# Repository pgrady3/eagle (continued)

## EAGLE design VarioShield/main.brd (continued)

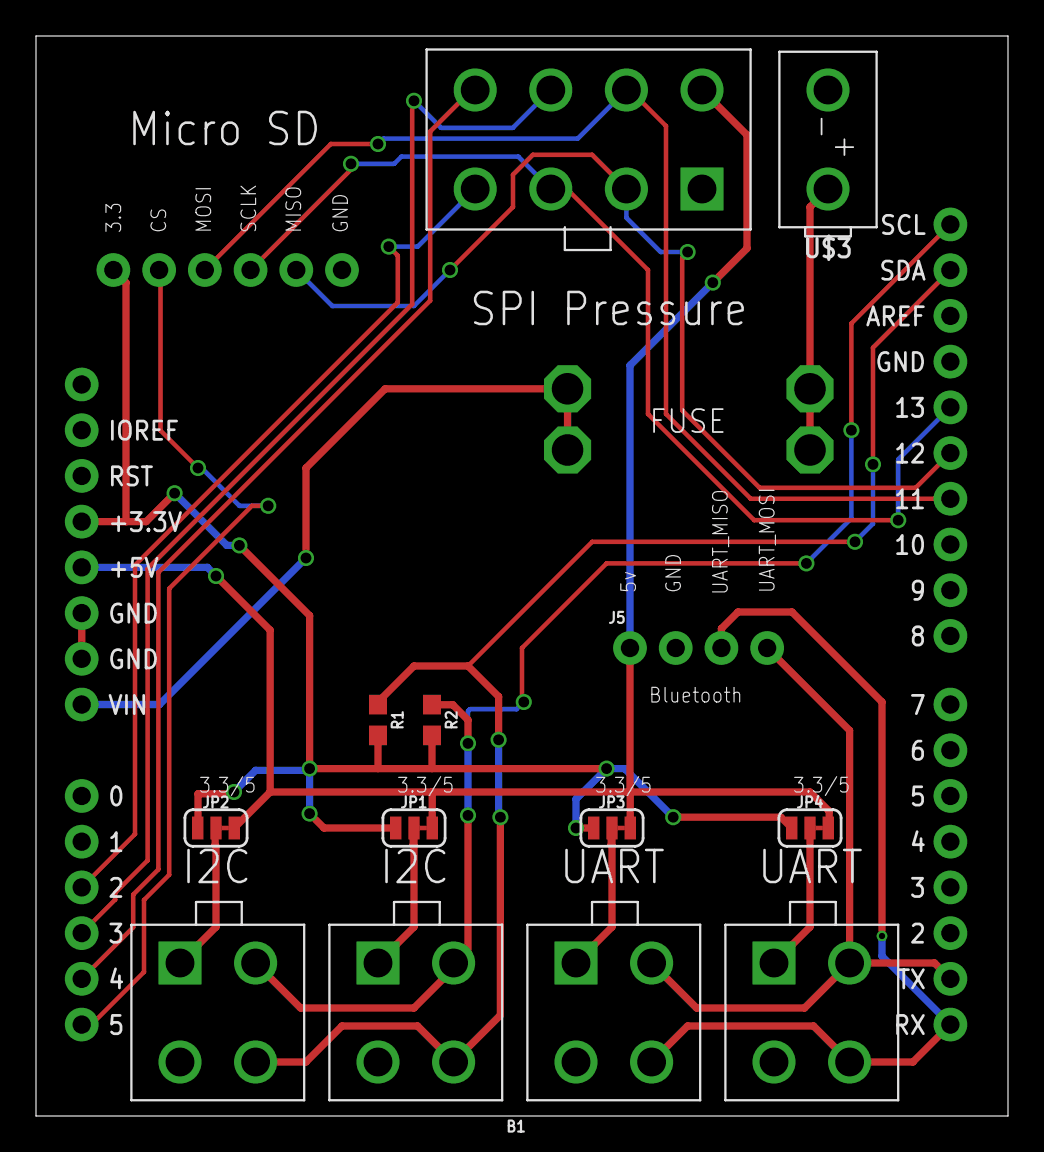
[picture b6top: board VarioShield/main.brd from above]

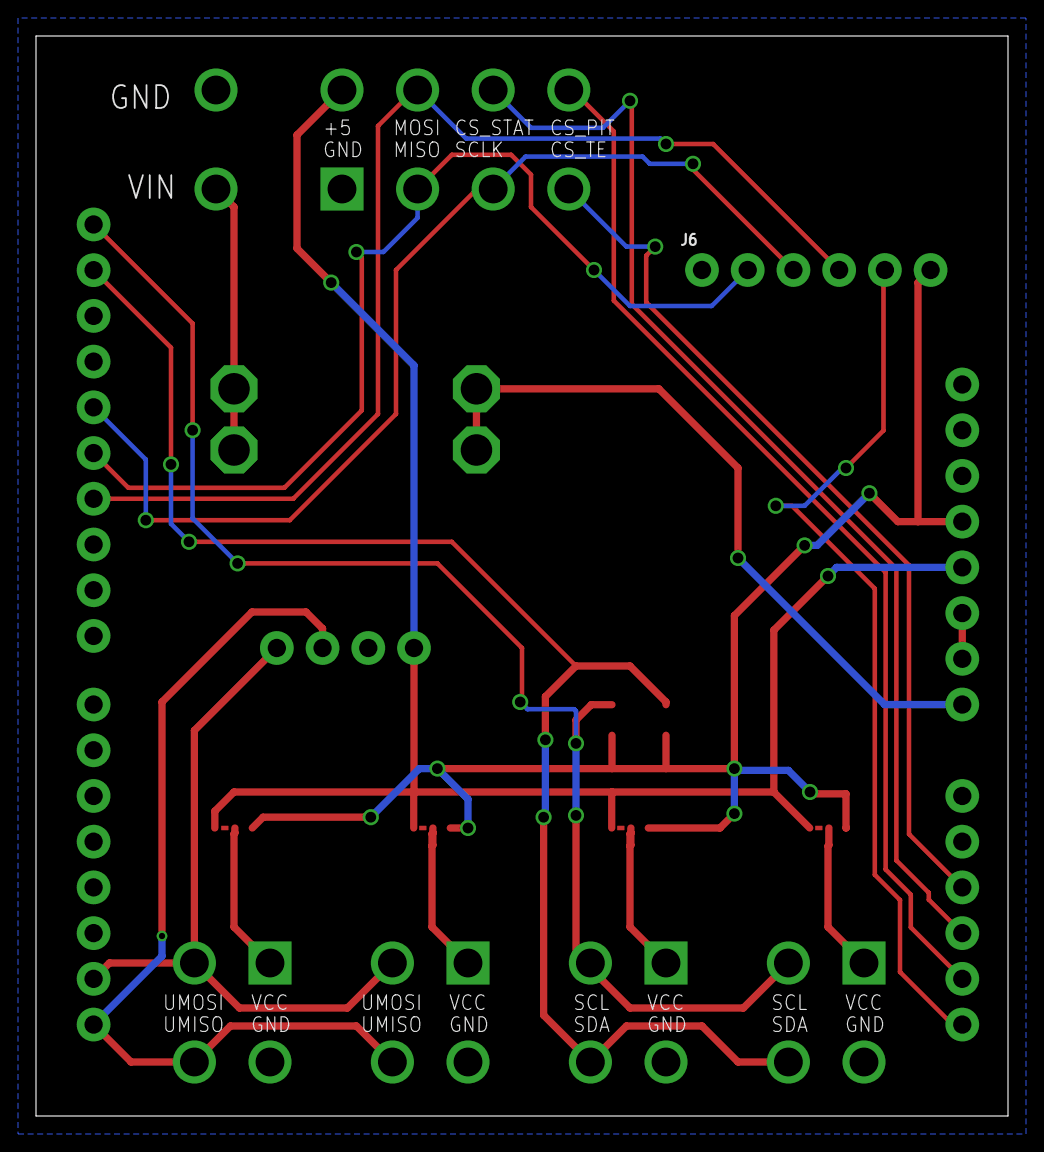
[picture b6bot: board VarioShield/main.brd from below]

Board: 2 copper layers, 54.0 x 60.0 mm, 16 parts (2 on the bottom side), 20 nets.

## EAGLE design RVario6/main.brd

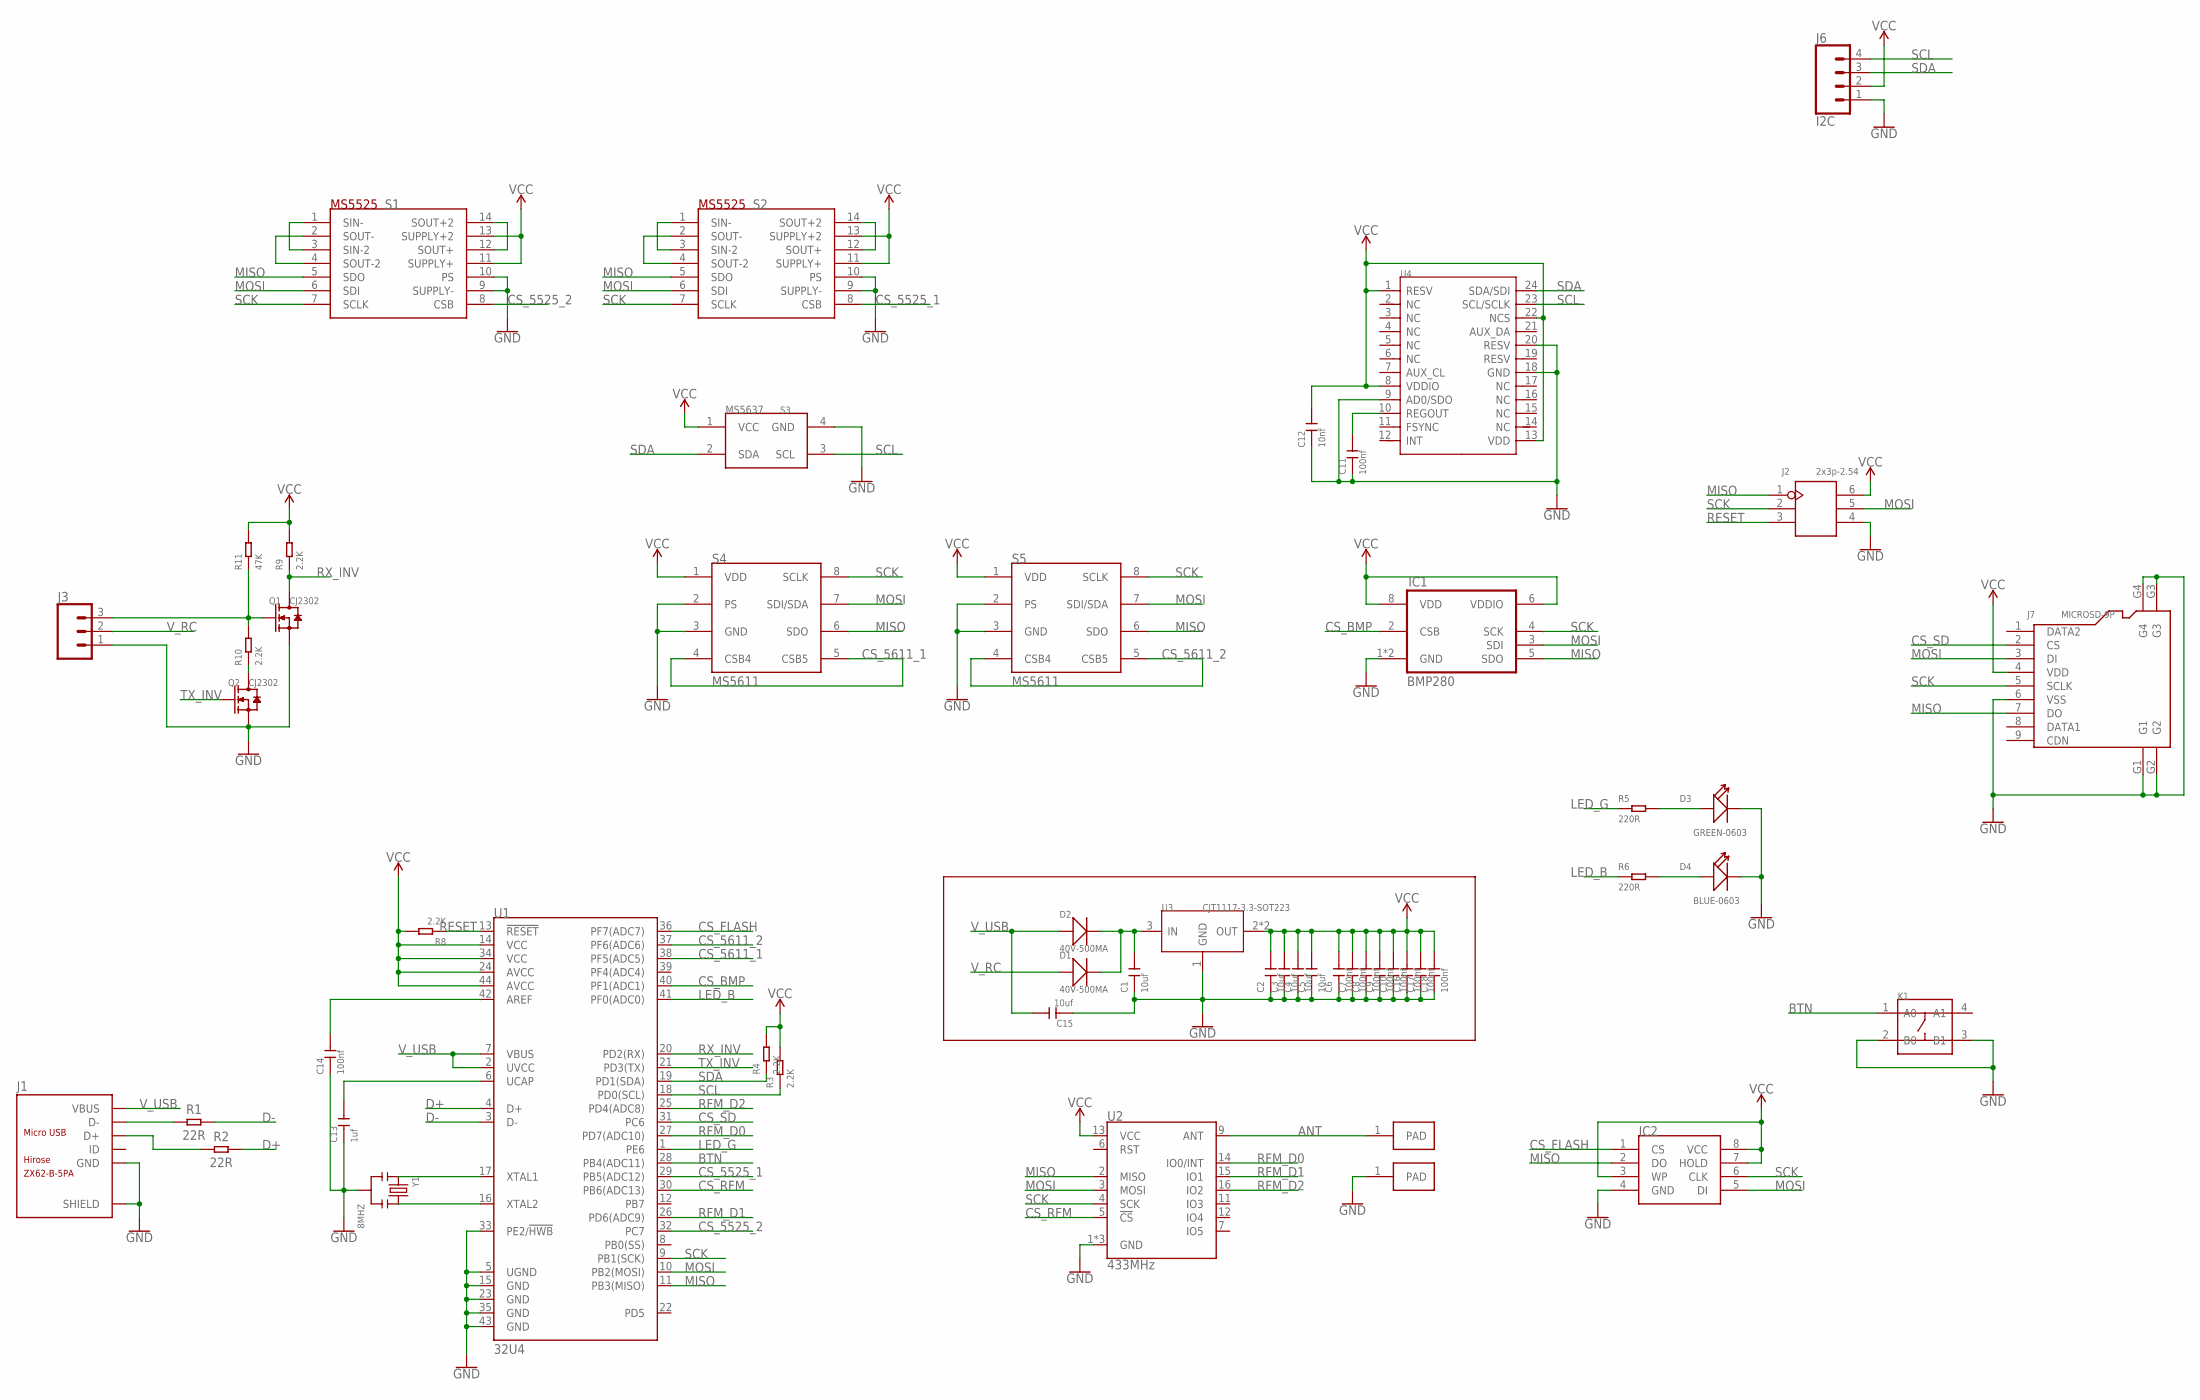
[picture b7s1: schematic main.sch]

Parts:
C1, C2, C3, C4, C5, C15: 10uf; C0805
C6, C7, C8, C9, C10, C11, C14, C16, C17, C18: 100nf; C0603
C12: 10nf; C0603
C13: 1uf; C0603
D1, D2: 40V-500MA; SOD-123
D3: GREEN-0603; LED-0603
D4: BLUE-0603; LED-0603
IC1: BMP280
IC2: W25Q32BVWSON8_6X5; SON127P600X500X75-8
J1: ZX62-B-5PA; MICRO-USB5+6P-SMD-0.65-AB
J2: 2x3p-2.54; H2X3-2.54
J3: CONN_03; 1X03
J6: I2C; 1X04
J7: MICROSD-9P; MICRO-SD9+4P-SMD-16.1X14.5X1.85MM
K1: SMD-SWITCH-TACTILE-SPST-NO(4P-D6.0MM); SW4-SMD-6.0X6.0X5.0MM
Q1, Q2: CJ2302; SOT-23
R1, R2: 22R; R0603
R3, R4, R8, R9, R10: 2.2K; R0603
R5, R6: 220R; R0603
R11: 47K; R0603
S1, S2: MS5525; SOIC14-WIDE
S3: MS5637
S4, S5: MS5611
U1: 32U4; QFN-44-NOPAD_1:1
U2: 433MHz; RFM69HCW-XXXS2
U3: CJT1117-3.3-SOT223; SOT-223
U4: MOTION/POSITION-MPU-9250(QFN24G); QFN24G-0.4-3X3MM
U$1, U$2: PADPAD_2.5X1.5; PAD_2.5X1.5
Y1: 8MHZ; X3-SMD-3.6X1.3X0.8MM

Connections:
ANT: U2.9 (ANT), U$2.1
BTN: K1.1 (A0), U1.28 (PB4(ADC11))
CS_5525_1: S2.8 (CSB), U1.29 (PB5(ADC12))
CS_5525_2: S1.8 (CSB), U1.32 (PC7)
CS_5611_1: S4.4 (CSB4), S4.5 (CSB5), U1.38 (PF5(ADC5))
CS_5611_2: S5.4 (CSB4), S5.5 (CSB5), U1.37 (PF6(ADC6))
CS_BMP: IC1.2 (CSB), U1.40 (PF1(ADC1))
CS_FLASH: IC2.1 (CS), U1.36 (PF7(ADC7))
CS_RFM: U1.30 (PB6(ADC13)), U2.5 (!CS)
CS_SD: J7.2 (CS), U1.31 (PC6)
D+: R2.2, U1.4 (D+)
D-: R1.2, U1.3 (D-)
GND: C1.1, C2.1, C3.1, C4.1, C5.1, C6.1, C7.1, C8.1, C9.1, C10.1, C11.1, C12.1, C13.1, C14.1, C15.1, C16.1, C17.1, C18.1, D3.-, D4.-, IC1.1 (GND), IC1.7 (GND), IC2.4 (GND), J1.5 (GND), J1.P1 (SHIELD), J1.P2 (SHIELD), J1.P3 (SHIELD), J1.P4 (SHIELD), J1.P5 (SHIELD), J1.P6 (SHIELD), J2.4, J3.1, J6.1, J7.6 (VSS), J7.G1, J7.G2, J7.G3, J7.G4, K1.2 (B0), K1.3 (B1), Q1.2 (S), Q2.2 (S), S1.9 (SUPPLY-), S1.10 (PS), S2.9 (SUPPLY-), S2.10 (PS), S3.4 (GND), S4.2 (PS), S4.3 (GND), S5.2 (PS), S5.3 (GND), U1.5 (UGND), U1.15 (GND), U1.23 (GND), U1.33 (PE2/!HWB), U1.35 (GND), U1.43 (GND), U2.1 (GND), U2.8 (GND), U2.10 (GND), U3.1 (GND), U4.9 (AD0/SDO), U4.18 (GND), U4.20 (RESV), U$1.1, Y1.2
LED_B: R6.1, U1.41 (PF0(ADC0))
LED_G: R5.1, U1.1 (PE6)
MISO: IC1.5 (SDO), IC2.2 (DO), J2.1, J7.7 (DO), S1.5 (SDO), S2.5 (SDO), S4.6 (SDO), S5.6 (SDO), U1.11 (PB3(MISO)), U2.2 (MISO)
MOSI: IC1.3 (SDI), IC2.5 (DI), J2.5, J7.3 (DI), S1.6 (SDI), S2.6 (SDI), S4.7 (SDI/SDA), S5.7 (SDI/SDA), U1.10 (PB2(MOSI)), U2.3 (MOSI)
unnamed: U1.17 (XTAL1), Y1.1
unnamed: U1.16 (XTAL2), Y1.3
unnamed: J1.2 (D-), R1.1
unnamed: J1.3 (D+), R2.1
unnamed: C1.2, D1.-, D2.-, U3.3 (IN)
unnamed: Q2.3 (D), R10.1
unnamed: S2.1 (SIN-), S2.3 (SIN-2)
unnamed: S2.2 (SOUT-), S2.4 (SOUT-2)
unnamed: S2.12 (SOUT+), S2.14 (SOUT+2)
unnamed: C11.2, U4.10 (REGOUT)
unnamed: S1.1 (SIN-), S1.3 (SIN-2)
unnamed: S1.2 (SOUT-), S1.4 (SOUT-2)
unnamed: S1.12 (SOUT+), S1.14 (SOUT+2)
unnamed: D3.+, R5.2
unnamed: D4.+, R6.2
unnamed: C13.2, U1.6 (UCAP)
unnamed: C14.2, U1.42 (AREF)
RC_IN: J3.3, Q1.1 (G), R10.2, R11.1
RESET: J2.3, R8.1, U1.13 (!RESET)
RFM_D0: U1.27 (PD7(ADC10)), U2.14 (IO0/INT)
RFM_D1: U1.26 (PD6(ADC9)), U2.15 (IO1)
RFM_D2: U1.25 (PD4(ADC8)), U2.16 (IO2)
RX_INV: Q1.3 (D), R9.1, U1.20 (PD2(RX))
SCK: IC1.4 (SCK), IC2.6 (CLK), J2.2, J7.5 (SCLK), S1.7 (SCLK), S2.7 (SCLK), S4.8 (SCLK), S5.8 (SCLK), U1.9 (PB1(SCK)), U2.4 (SCK)
SCL: J6.4, R3.1, S3.3 (SCL), U1.18 (PD0(SCL)), U4.23 (SCL/SCLK)
SDA: J6.3, R4.1, S3.2 (SDA), U1.19 (PD1(SDA)), U4.24 (SDA/SDI)
TX_INV: Q2.1 (G), U1.21 (PD3(TX))
VCC: C2.2, C3.2, C4.2, C5.2, C6.2, C7.2, C8.2, C9.2, C10.2, C12.2, C16.2, C17.2, C18.2, IC1.6 (VDDIO), IC1.8 (VDD), IC2.3 (WP), IC2.7 (HOLD), IC2.8 (VCC), J2.6, J6.2, J7.4 (VDD), R3.2, R4.2, R8.2, R9.2, R11.2, S1.11 (SUPPLY+), S1.13 (SUPPLY+2), S2.11 (SUPPLY+), S2.13 (SUPPLY+2), S3.1 (VCC), S4.1 (VDD), S5.1 (VDD), U1.14 (VCC), U1.24 (AVCC), U1.34 (VCC), U1.44 (AVCC), U2.13 (VCC), U3.2 (OUT), U3.TER (OUT), U4.1 (RESV), U4.8 (VDDIO), U4.13 (VDD), U4.22 (NCS)
V_RC: D1.+, J3.2
V_USB: C15.2, D2.+, J1.1 (VBUS), U1.2 (UVCC), U1.7 (VBUS)

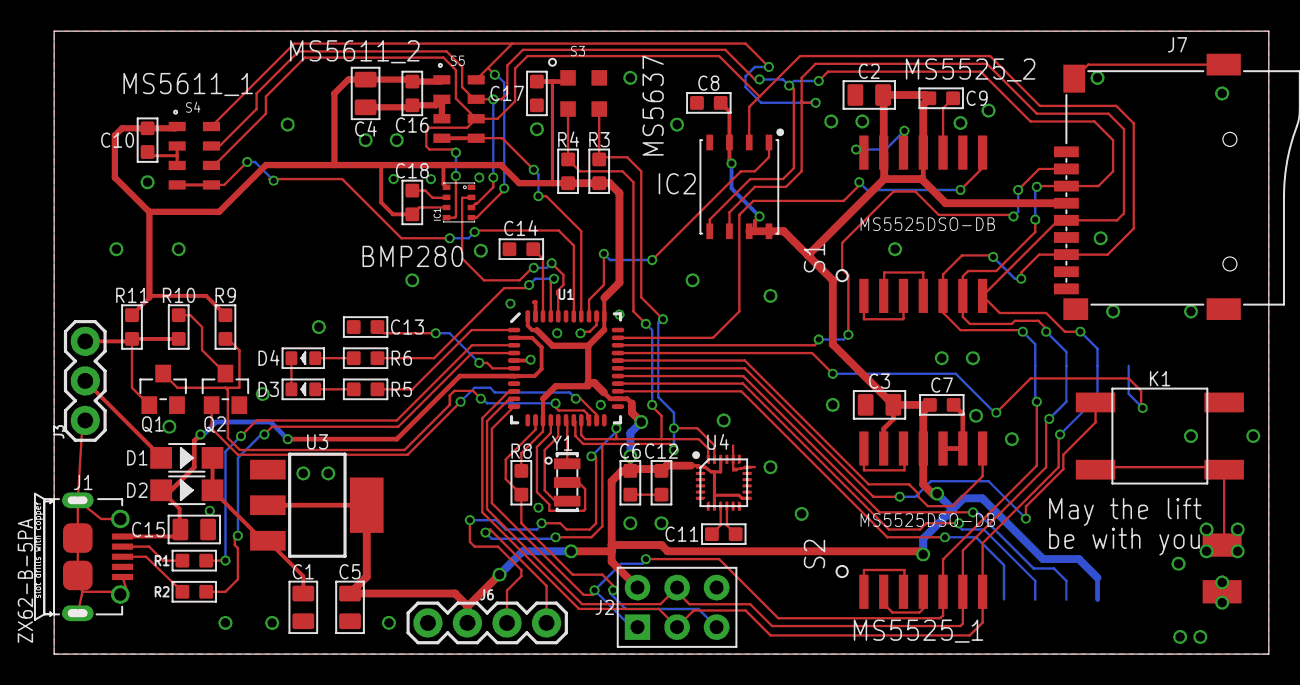
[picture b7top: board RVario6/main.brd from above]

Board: 2 copper layers, 78.6 x 40.0 mm, 54 parts (1 on the bottom side), 47 nets.

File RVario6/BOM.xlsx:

Designator | MPN/Seeed SKU | Qty | Link | Price
U1 | ATMEGA32U4-MUR | 1 | 310010016 | 4.0999999999999996 | AVR |  |  |  |  | 4.0999999999999996 |  | 9.2879999999999967
J1 | ZX62D-B-5P8 | 1 | 320010005 | 0.12 | Micro USB |  |  |  |  | 0.12
R1,R2 | RC0603JR-0722RL | 2 | 301010289 | 0.01 | 22 ohm 0603 |  |  |  |  | 0.02
Y1 | CSTCE8M00G55-RO | 1 | 306010053 | 0.188 | 8MHz crystal |  |  |  |  | 0.188
D1,D2 | B0540W | 2 | 304020012 | 0.03 | Schottkey |  |  |  |  | 0.06
U3 | CJT1117-3.3 | 1 | 310030097 | 0.08 | 3.3V VREG |  |  |  |  | 0.08
C1,C2,C3,C4,C5,C15 | CC0805KKX5R8BB106 | 6 | 302010178 | 0.02 | 10uF cap |  |  |  |  | 0.12
C6,C7,C8,C9,C10,C11,C14,C16,C17,C18 | CC0603KRX7R9BB104 | 10 | 302010138 | 0.01 | 0.1uF cap |  |  |  |  | 0.1
R3,R4,R8,R9,R10 | RC0603JR-072K2L | 5 | 301010124 | 0.01 | 2.2k res |  |  |  |  | 0.05
C12 | CC0603KRX7R9BB103 | 1 | 302010140 | 0.01 | 10nF cap |  |  |  |  | 0.01
IC1 | BMP280 | 1 | 314030010 | 1.07 | BMP280 |  |  |  |  | 1.07
D3 | 19-217-G7C-AN1P2-3T | 1 | 304090043 | 0.02 | LED GREEN |  |  |  |  | 0.02
D4 | 19-217-BHC-ZL1M2RY-3T | 1 | 304090045 | 0.02 | LED BLUE |  |  |  |  | 0.02
R5,R6 | RC0603JR-07220RL | 2 | 301010163 | 0.01 | 220 ohm |  |  |  |  | 0.02
J2 | P125-12A1BS116A1 | 1 | 320020077 | 0.01 | ISP header |  |  |  |  | 0.01
IC2 | W25Q32BVZPIP | 1 | 310090078 | 0.26 | 4MB flash |  |  |  |  | 0.26
C13 | CC0603KRX7R8BB105 | 1 | 302010139 | 0.01 | 1uF cap |  |  |  |  | 0.01
U4 | MPU-9250 | 1 | 314990005 | 2.8 | MPU9250 |  |  |  |  | 2.8
K1 | DTSM-62K-S-V-T/R | 1 | 311020004 | 0.05 | SMD btn |  |  |  |  | 0.05
J7 | TF-01 | 1 | 320090008 | 0.11 | SD card holder |  |  |  |  | 0.11
Q1,Q2 | CJ2302 | 2 | 305030015 | 0.03 | NFET |  |  |  |  | 0.06
R11 | RC0603JR-0747KL | 1 | 301010084 | 0.01 | 47k resistor |  |  |  |  | 0.01
 |  |  |  |  |  |  |  |  |  | 0
 |  |  |  |  |  |  |  |  |  | 0
 |  |  |  |  |  |  |  |  |  | 0
 |  |  |  |  |  |  |  |  |  | 0
 |  |  |  |  |  |  |  |  |  | 0
 |  |  |  |  |  |  |  |  |  | 0

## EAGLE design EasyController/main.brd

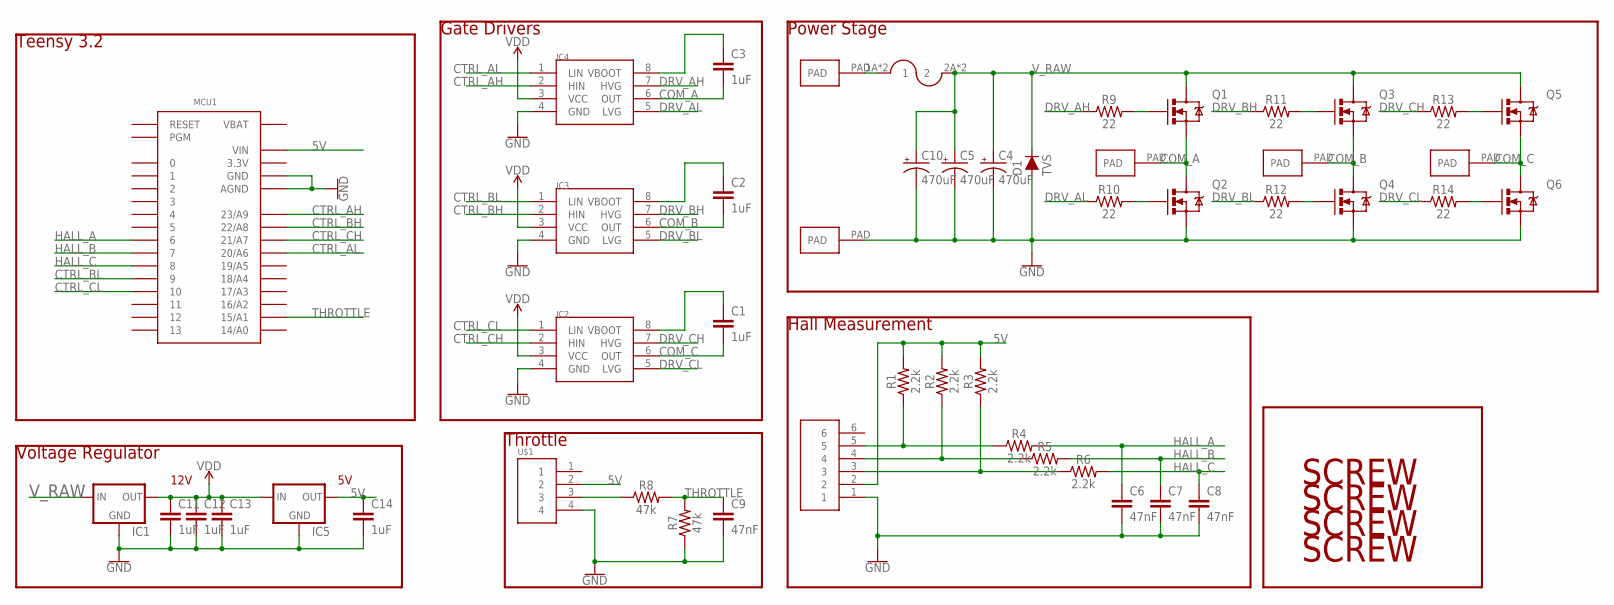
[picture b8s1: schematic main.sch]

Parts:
C1, C2, C3, C11, C12, C13, C14: 1uF; CAP-PTH-SMALL-KIT
C4, C5, C10: 470uF; CPOL-RADIAL-5MM-10MM
C6, C7, C8, C9: 47nF; CAP-PTH-SMALL-KIT
D1: TVS; DIODE-1N4001
IC1: V_REG_78XX; V78W_BACKWARDS
IC2, IC3, IC4: L6387EDIP8; DIP762W53P254L1092H508Q8B
IC5: V_REG_78XXTO-92_UNTESTED; TO-92
J3: FUSE; AUTO_FUSE
MCU1: TEENSY_3.0_BASIC
Q1, Q2, Q3, Q4, Q5, Q6: MOSFET-NCHANNELTO-220-FLAT; TO-220-FLAT
R1, R2, R3, R4, R5, R6: 2.2k; AXIAL-0.3
R7, R8: 47k; AXIAL-0.3
R9, R10, R11, R12, R13, R14: 22; AXIAL-0.3
U$1: HEADER4VALULOK; 4PINVALULOK
U$2: HEADER6; 6PINVALULOK
U$4, U$5, U$6, U$7, U$8: PAD
U$10, U$11, U$12, U$13: SCREW; M3HOLE

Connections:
3.3V: MCU1.3.3V, MCU1.3.3V1 (3.3V)
5V: C14.1, IC5.1 (OUT), MCU1.VIN, R1.P$2 (2), R2.P$2 (2), R3.P$2 (2), U$1.2, U$2.2
COM_A: C3.2, IC4.6 (OUT), Q1.3 (S), Q2.2 (D), Q2.PAD (D), U$6.PAD
COM_B: C2.2, IC3.6 (OUT), Q3.3 (S), Q4.2 (D), Q4.PAD (D), U$7.PAD
COM_C: C1.2, IC2.6 (OUT), Q5.3 (S), Q6.2 (D), Q6.PAD (D), U$8.PAD
CTRL_AH: IC4.2 (HIN), MCU1.23/A9
CTRL_AL: IC4.1 (LIN), MCU1.20/A6
CTRL_BH: IC3.2 (HIN), MCU1.22/A8
CTRL_BL: IC3.1 (LIN), MCU1.9
CTRL_CH: IC2.2 (HIN), MCU1.21/A7
CTRL_CL: IC2.1 (LIN), MCU1.10
DRV_AH: IC4.7 (HVG), R9.P$1 (1)
DRV_AL: IC4.5 (LVG), R10.P$1 (1)
DRV_BH: IC3.7 (HVG), R11.P$1 (1)
DRV_BL: IC3.5 (LVG), R12.P$1 (1)
DRV_CH: IC2.7 (HVG), R13.P$1 (1)
DRV_CL: IC2.5 (LVG), R14.P$1 (1)
GND: C4.-, C5.-, C6.2, C7.2, C8.2, C9.2, C10.-, C11.2, C12.2, C13.2, C14.2, D1.A, IC1.GND, IC2.4 (GND), IC3.4 (GND), IC4.4 (GND), IC5.2 (GND), MCU1.AGND, MCU1.GND, MCU1.GND1 (GND), Q2.3 (S), Q4.3 (S), Q6.3 (S), R7.P$1 (1), U$1.4, U$2.1, U$5.PAD
HALL_A: C6.1, MCU1.6, R4.P$2 (2)
HALL_B: C7.1, MCU1.7, R5.P$2 (2)
HALL_C: C8.1, MCU1.8, R6.P$2 (2)
unnamed: C1.1, IC2.8 (VBOOT)
unnamed: R3.P$1 (1), R6.P$1 (1), U$2.3
unnamed: C2.1, IC3.8 (VBOOT)
unnamed: R2.P$1 (1), R5.P$1 (1), U$2.4
unnamed: C3.1, IC4.8 (VBOOT)
unnamed: R1.P$1 (1), R4.P$1 (1), U$2.5
unnamed: R8.P$1 (1), U$1.3
unnamed: Q1.1 (G), R9.P$2 (2)
unnamed: Q2.1 (G), R10.P$2 (2)
unnamed: Q3.1 (G), R11.P$2 (2)
unnamed: Q4.1 (G), R12.P$2 (2)
unnamed: Q5.1 (G), R13.P$2 (2)
unnamed: Q6.1 (G), R14.P$2 (2)
THROTTLE: C9.1, MCU1.15/A1, R7.P$2 (2), R8.P$2 (2)
VBAT: MCU1.VBAT
VDD: C11.1, C12.1, C13.1, IC1.OUT, IC2.3 (VCC), IC3.3 (VCC), IC4.3 (VCC), IC5.3 (IN)
V_PREFUSE: J3.1A (1), J3.1B (1), U$4.PAD
V_RAW: C4.+, C5.+, C10.+, D1.C, IC1.IN, J3.2A (2), J3.2B (2), Q1.2 (D), Q1.PAD (D), Q3.2 (D), Q3.PAD (D), Q5.2 (D), Q5.PAD (D)

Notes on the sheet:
Power Stage
Hall Measurement
Gate Drivers
Throttle
Teensy 3.2
Voltage Regulator
12V

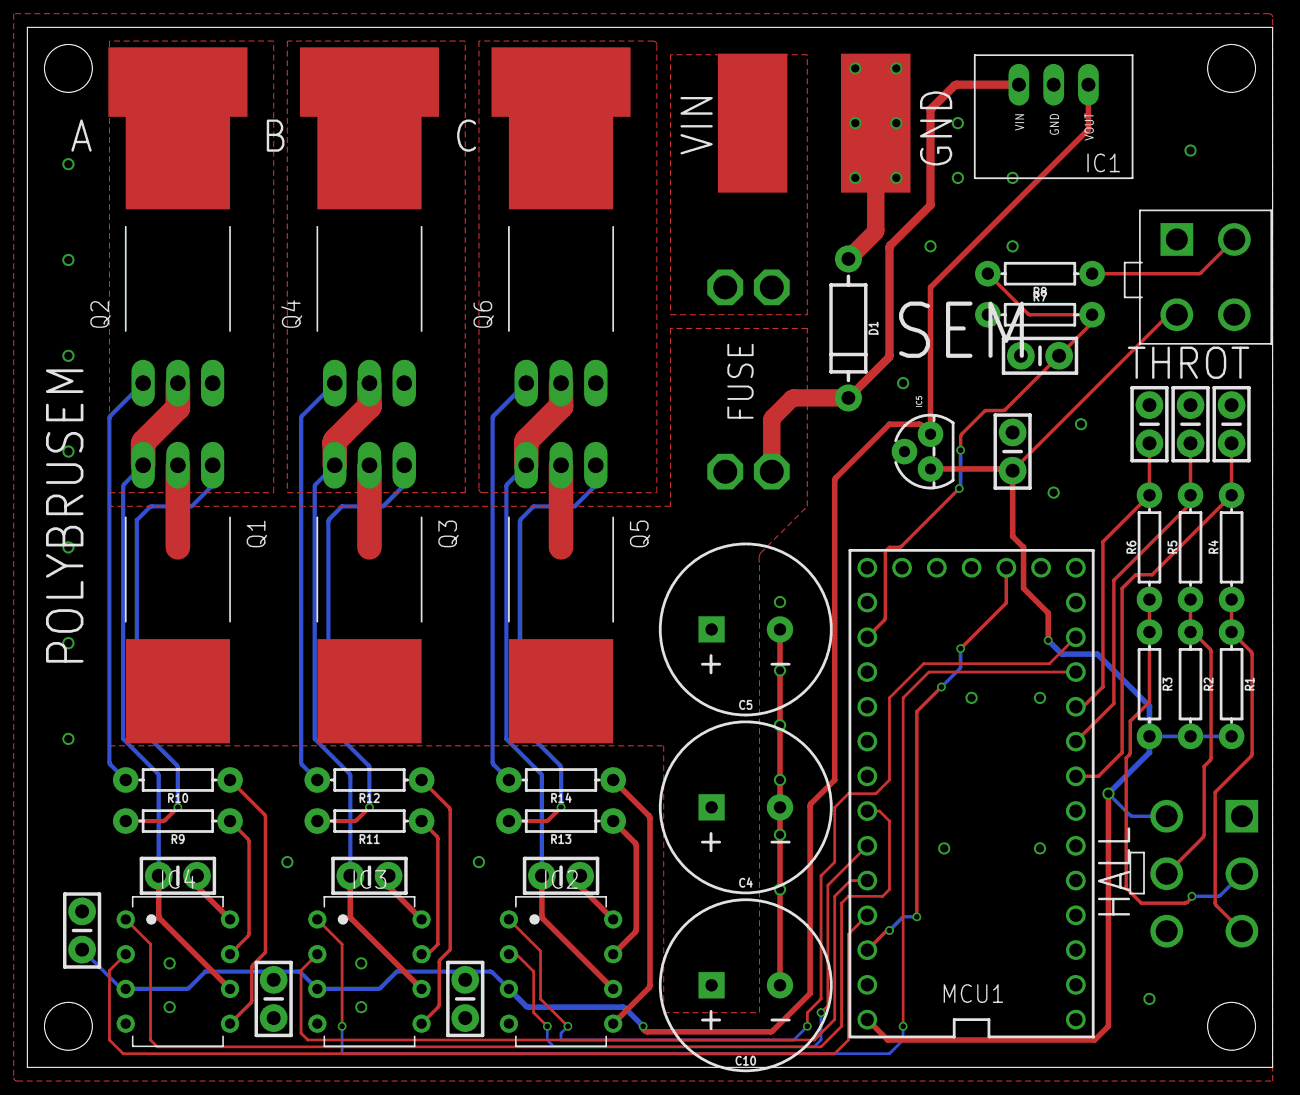
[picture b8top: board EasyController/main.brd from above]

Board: 2 copper layers, 91.0 x 76.0 mm, 53 parts (0 on the bottom side), 38 nets.

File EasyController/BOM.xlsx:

Digikey part # | Designator | Qty | Price | Description
497-6219-5-ND | IC2,IC3,IC4 | 3 | 1.66 | Gate driver |  |  |  | 4.9799999999999995 |  | 68.369999999999976
445-173257-1-ND | C1,C2,C3,C11,C12,C13,C14 | 7 | 0.33 | 1uF cap |  |  |  | 2.31
IRFB7730PBF-ND | Q1,Q2,Q3,Q4,Q5,Q6 | 6 | 3.51 | NFET |  |  |  | 21.06
P6KE68CALFCT-ND | D1 | 1 | 0.47 | TVS Diode |  |  |  | 0.47
565-3994-ND | C4,C5,C10 | 3 | 1.1499999999999999 | 470uF cap |  |  |  | 3.4499999999999997
CF14JT2K20CT-ND | R1,R2,R3,R4,R5,R6 | 6 | 0.1 | 2.2k resistor |  |  |  | 0.60000000000000009
BC1082CT-ND | C6,C7,C8,C9 | 3 | 0.16 | 47nF cap |  |  |  | 0.48
36-3557-2-ND | J3 | 1 | 1.03 | Fuse holder |  |  |  | 1.03
1470-4533-ND | IC1 | 1 | 8 | Voltage Regulator |  |  |  | 8
CF14JT47K0CT-ND | R7,R8 | 1 | 0.1 | 47k resistor |  |  |  | 0.1
1568-1231-ND | MCU1 | 1 | 22.5 | Teensy 3.2 |  |  |  | 22.5
CF14JT22R0CT-ND | R9,R10,R11,R12,R13,R14 | 6 | 0.1 | 22 ohm |  |  |  | 0.60000000000000009
497-1184-1-ND | IC5 | 1 | 0.35 | 5V Linear reg |  |  |  | 0.35
S1012EC-14-ND |  | 2 | 0.31 | 14 pin male header |  |  |  | 0.62
S7012-ND |  | 2 | 0.91 | 14 pin female header |  |  |  | 1.82
 |  |  |  |  |  |  |  | 0
345-1092-ND‎ |  |  |  | Heatsink
‎1168-1380-ND‎ |  |  |  | Thermal paste

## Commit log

2018-12-21 Added sparkfun eagle libs
2018-12-21 Added AVRVario and RVario5
2018-12-21 Added old libs
2019-01-11 Added RVario6 Eagle
2019-01-20 EasyController submitted to AllPCB
2019-01-20 Finished schematic RVario6
2019-02-03 Rvario6 updates
2019-02-12 EasyController and EasyTelemetry almost ready to submit
2019-02-12 Allpcb submit
2019-02-13 Updated boms and gerbers for Brunei
2019-02-13 Partiall routed
2019-02-14 partially routed
2019-02-14 done routing!
2019-02-14 Added silkscreen
2019-02-14 SEEED SUBMIT!!!!!
2019-03-14 Added cam and telemetry sch pdf
2019-04-29 Updated bom
2019-11-12 All PCB submit vario
2019-11-18 JLC submit
2019-12-20 Added error note....
2020-01-31 Added IMU board, vario base 2
2020-01-31 JLC submit. Forgot silkscreen.....
2020-04-25 IMU board submit, doesn't work
2020-04-25 Vario3 Submit
2023-03-29 Updated libs
